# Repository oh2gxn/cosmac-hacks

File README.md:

# cosmac-hacks
Various programs for the 1802 Membership Card

Due to my interests in both embedded / low-level programming and 
retro electronics, I started hacking with a modern version of the
70's COSMAC ELF.

## Hardware
Currently, I'm running these programs on the 1802 Membership Card (Rev. G) 
by Lee Hart et al.
http://www.retrotechnology.com/memship/memship.html

## Programming tips
In lack of better code format, I'm following the conventions at
http://www.ittybittycomputers.com/IttyBitty/ShortCor.htm

So, each of the bytes in the object code is represented by one row with the 
following fields:
- *address* in hex
- *binary code* in hex
- *label:* (optional)
- *mnemonic*
- *operand* (when applicable, sometimes represented by the next byte)
- *.. comment* (the two dots are the comment separator)

Example:
```
0003 E7 LOOP:   SEX 7  .. register address of a memory address
```

## List of current programs
The test programs from the 1802 Membership Card manual:
- `blinkQfast`: a test program flipping Q on/off as fast as possible
- `blinkQslow`: a similar test with a delay loop
- `valotin`: test for reading input switches and controlling output LEDs

There was no mention about a software licence, but I suppose sharing these simple examples falls into the category of "fair use". Besides, the comments and potential bugs are mine :)

My hack for testing RAM:
- `memtest`: The amount of RAM can be doubled by installing another 32k RAM
  chip and using the 16th address bit (and its inverse) for the chip output 
  enable pins. However, the bit-inverting FET in Rev. G might not work 
  reliably with all RAM chips, so there is a need for a test program.

## TODO: more programs...
At least the following are planned:
- `bytebeat`: This would require an 8-bit 8kHz "sound card" =)
- some recent revision of ETOPS?
- some equivalent of PAL Pixie (more HW)?

-Janne, OH2GXN

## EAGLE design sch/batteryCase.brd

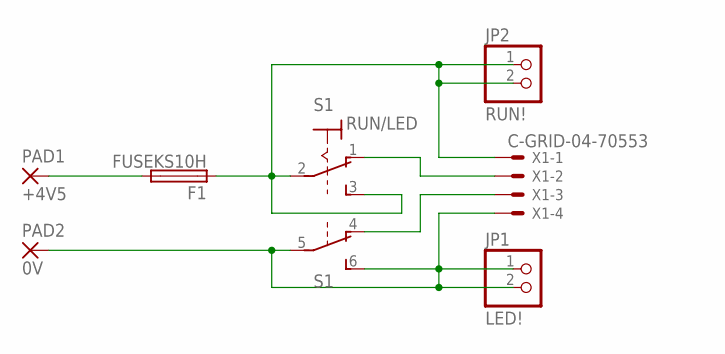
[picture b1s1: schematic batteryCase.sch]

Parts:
F1: FUSEKS10H; KS10H
JP1: LED!; 1X02/90
JP2: RUN!; 1X02/90
PAD1: +4V5; SMD2,54-5,08
PAD2: 0V; SMD2,54-5,08
S1: RUN/LED; M9040P2
X1: C-GRID-04-70553; 70553-04

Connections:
unnamed: F1.2, PAD1.1
unnamed: JP1.1, JP1.2, PAD2.1, S1.5, S1.6 (S), X1.4
unnamed: F1.1, JP2.1, JP2.2, S1.2, S1.3 (S), X1.1
unnamed: S1.1 (O), X1.2
unnamed: S1.4 (O), X1.3

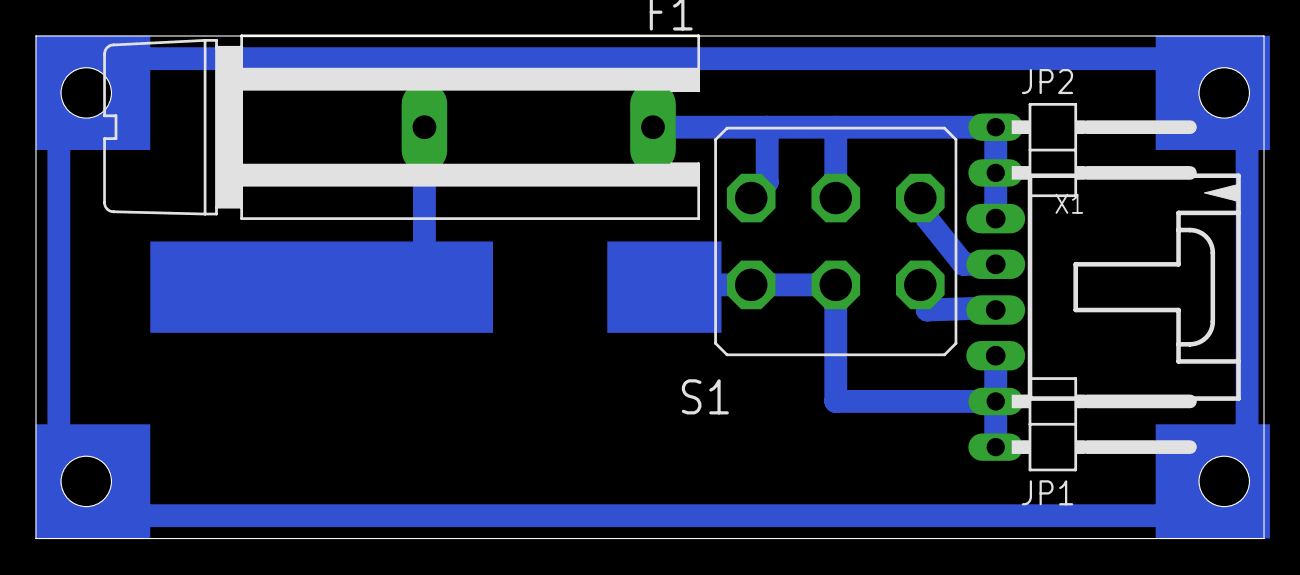
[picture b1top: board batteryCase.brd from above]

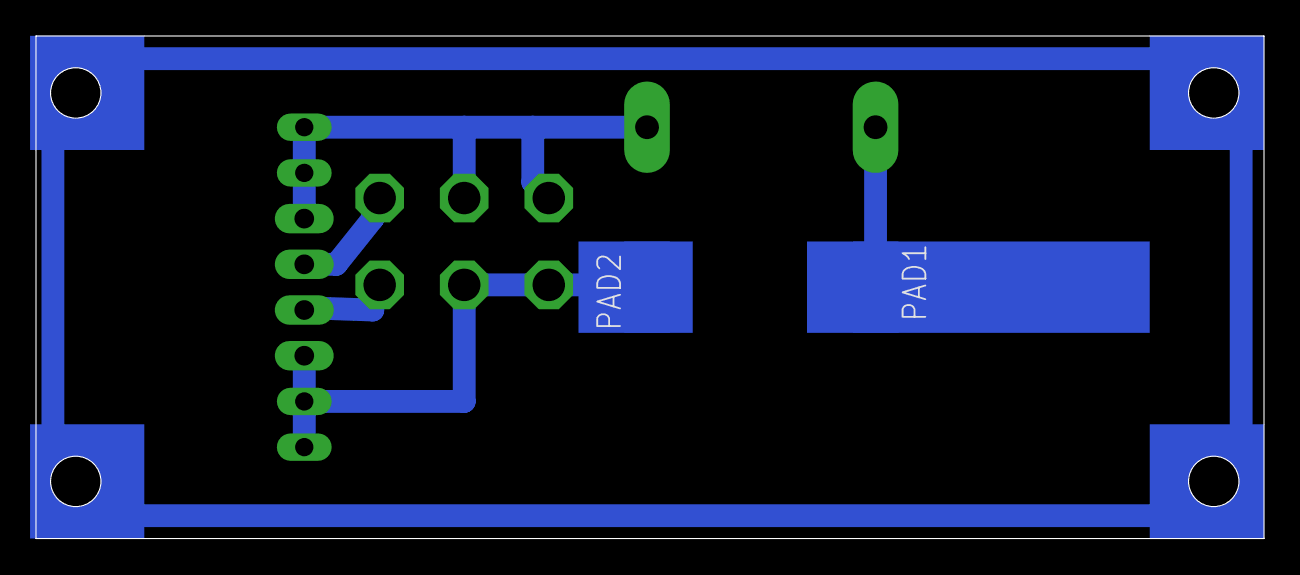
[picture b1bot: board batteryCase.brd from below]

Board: 2 copper layers, 68.2 x 27.9 mm, 7 parts (2 on the bottom side), 5 nets.

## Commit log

2015-10-09 Few links
2015-10-09 Some basics
2015-10-09 Consistent naming: 1802 Membership Card, not just some membership card
2015-10-09 Some more code
2015-10-10 Notes about the origin of first examples
2015-10-10 Started hacking memtest
2015-10-11 Rough idea of memtest, not sure about address bounds & inc/dec
2015-10-11 More memtest ideas
2015-10-11 Details to be debugged
2015-10-11 Seems legit, let's run
2015-10-11 Memtest runs, but lights up Q at the end: either there is a bug or my RAM has issues with 0x7Fnn for real.
2015-10-12 Bug found: OUT increments the pointer too
2015-10-13 Sacrificed one more register for decoupling display from testing. Seems to run fine with 32k RAM.
2015-10-13 More plans
2015-10-20 The minimal operating systems. Some cleanup required..
2015-10-20 Added UM61256 as U8: seems to work. TODO: rotating test pattern or something.
2015-11-08 Plans for a power source
2015-11-08 Fine tuning the 3LR12 board layout
2015-11-08 Better fuse holder and clearances
2015-11-09 Some copper plane for mechanical strength (and reminder about metal casing)
2015-11-10 Started sketching 8-bit audio HW, no idea of the clock or control yet
2015-11-14 8kHz HW clock, or maybe using SW and just tuning the CPU clock?
2015-11-18 HW sample clock by 555 timer
2015-11-19 Christmas lights :)
2015-11-20 Longer delay for memdump. Realized that R1 and R2 are used by ISR, so using R3-RF.
2015-11-20 Updated branch addresses too
2015-11-21 HW sample clock with delay / pulse width (even less SW control for ADC?)
2015-11-25 Example of dumping data to parallel port from a C program. TODO: input from shell pipe
2015-12-13 Breadboard prototype of sample clock: voltage regularization still missing
